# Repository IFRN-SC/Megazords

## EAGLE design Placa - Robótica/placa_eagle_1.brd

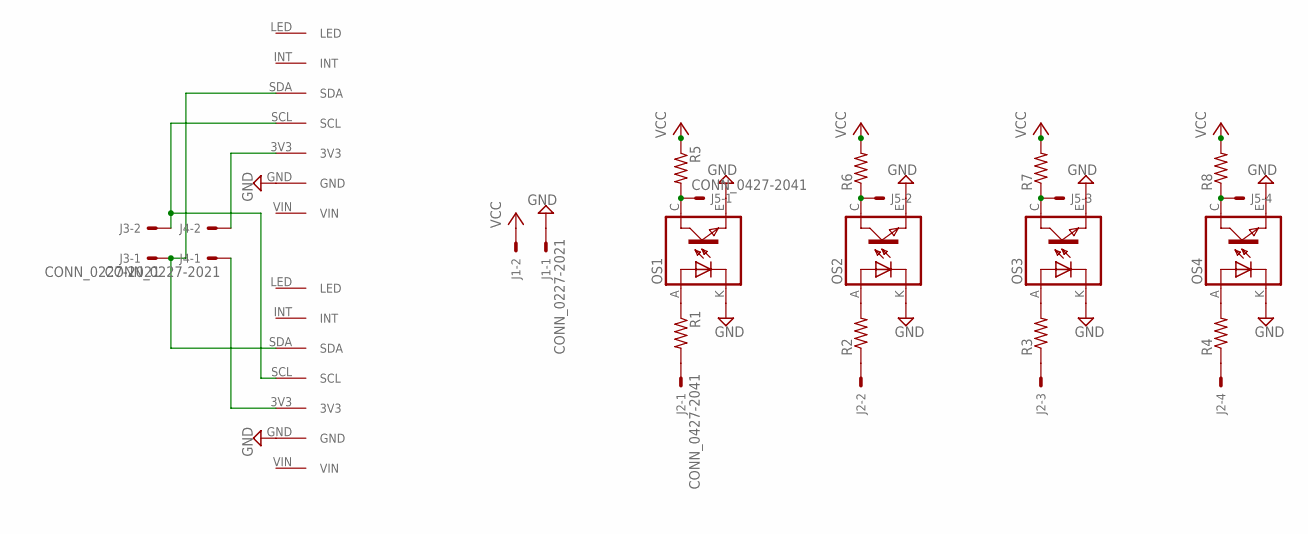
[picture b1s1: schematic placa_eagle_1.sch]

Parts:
J1, J3, J4: CONN_0227-2021; 6410-02
J2, J5: CONN_0427-2041; 6410-04
OS1, OS2, OS3, OS4: TCRT5000
R1, R2, R3, R4, R5, R6, R7, R8: R-US_0204/7; 0204/7
TCS1, TCS2: TCS34725

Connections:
GND: J1.1, OS1.E (EMITTER), OS1.K (CATHODE), OS2.E (EMITTER), OS2.K (CATHODE), OS3.E (EMITTER), OS3.K (CATHODE), OS4.E (EMITTER), OS4.K (CATHODE), TCS1.GND, TCS2.GND
unnamed: OS1.A (ANODE), R1.1
unnamed: OS2.A (ANODE), R2.2
unnamed: OS3.A (ANODE), R3.2
unnamed: OS4.A (ANODE), R4.2
unnamed: J5.1, OS1.C (COLLECTOR), R5.2
unnamed: J5.2, OS2.C (COLLECTOR), R6.1
unnamed: J5.3, OS3.C (COLLECTOR), R7.1
unnamed: J5.4, OS4.C (COLLECTOR), R8.1
unnamed: J2.1, R1.2
unnamed: J2.2, R2.1
unnamed: J2.3, R3.1
unnamed: J2.4, R4.1
unnamed: J4.2, TCS1.3V3
unnamed: J4.1, TCS2.3V3
unnamed: J3.1, TCS1.SDA, TCS2.SDA
unnamed: J3.2, TCS1.SCL, TCS2.SCL
VCC: J1.2, R5.1, R6.2, R7.2, R8.2

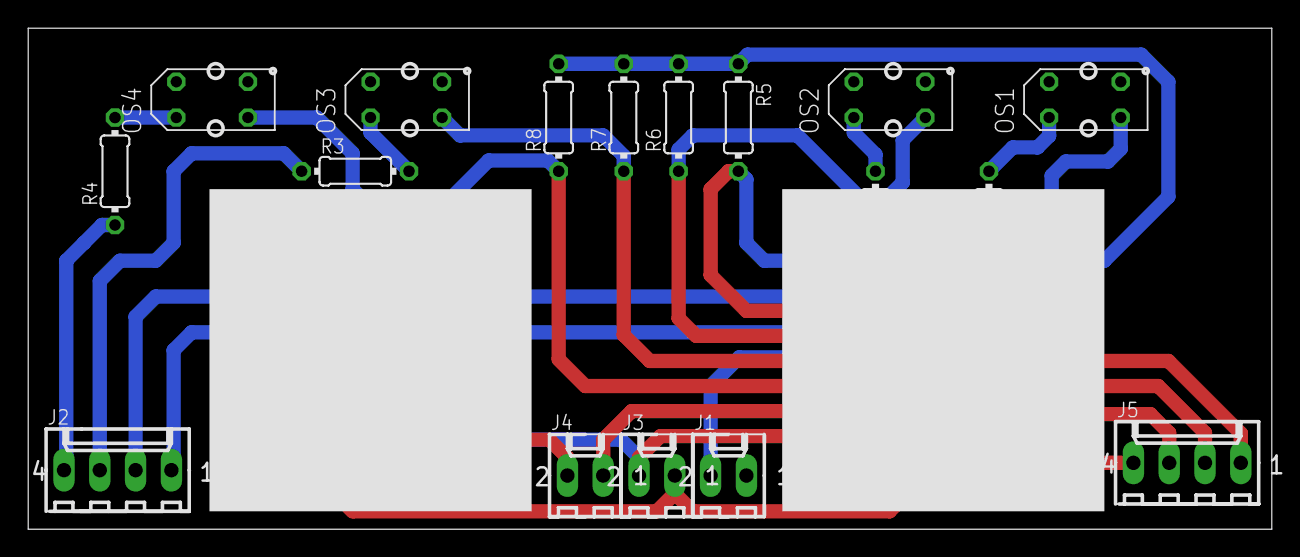
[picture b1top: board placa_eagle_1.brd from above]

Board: 2 copper layers, 88.2 x 35.5 mm, 19 parts (0 on the bottom side), 18 nets.

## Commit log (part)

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2018-04-11 Adcionando um novo codigo
2018-04-11 Uma pasta foi modificada
2018-04-11 Os valores de tensao dos motores foram modificados
2018-04-11 Foram adicionados as primeiras classes orientadas a objetos
2018-04-12 Alteração no comentario
2018-04-12 deixe de onda
2018-04-12 modifição na ordem das funcoes dos sensores
2018-04-16 Começo de codigo na função seguirLinha da classe estrategia
2018-04-16 Descomentei o codigo das funcoes dos sensores mais esquerdo e mais direito
2018-04-16 adcionei o objeto da classe Sensores nas funcoes de seguir linha
2018-04-17 Criação da classe Movimento
2018-04-17 Foi adcionada a função branco_branco_preto_preto_branco
2018-04-17 Foi criado um objeto da classe Movimento
2018-04-17 mudança das funcoes privadas para publicas e acrescimo da funcao parar
2018-04-17 Alteracao nos valores das medias
2018-04-18 transformei as funções para definir o branco de private para public
2018-04-18 Foi adcionado a função BPPB e as constantes repetidas de outra classe foram excluídas
2018-04-18 Foi criada a função voltar
2018-04-25 Calibracao foi incluido na classe Sensores, e um objeto foi criado
2018-05-04 Adição do codigo do sonar
2018-05-08 Foi adcionada a funcao detectouObstaculo
2018-05-09 Foi criada a classe Sensores.cpp
2018-05-09 moveu codigo sensores->estrategia
    foi realizada a mudança do código da classe sensores para a classe estratégia. Com isso foi necessário mudar funções de privada para pública
2018-05-10 Alteração no valor das medias dos sensores de refletancia e na posiçao da chave da função detectouObstaculo
2018-05-10 Foi adicionada a funcao desviarOPbstaculo dentro da funcao executar
2018-05-10 alteração nos valores das medias dos sensores de refletancia
2018-05-15 mudei o valor da constante PNEU_VOLTA
2018-05-15 sensores de refletância
    foi adicionado cinco funções para seguir linha.
2018-05-15 desviar obstaculo
    foi adicionado as funções da classe movimento no código de desviar obstaculo, e foi ajustado os valores para a execução do desviar.
2018-05-15 Criação do arquivo de Calibracao
2018-05-15 os dados foram movidos para o arquivo Calibracao.cpp
2018-05-15 desviar obstaculo
    foi regulado os valores para a execução de desviar o obstaculo.
2018-05-15 mudei o valor da constante PNEU_ANDA e PNEU_VOLTA
2018-05-15 foi ajustado o valor do delay
2018-05-23 desviar obstaculo
    foi iniciado o codigo de desviar obstaculo utilizando o sonar lateral
2018-05-23 moviento
    mudei os valores do robo.acionarMotores
2018-06-05 inclusao da classe Calibracao e uso da funcao
2018-06-05 Criação de funcoes
2018-06-05 Uso da função MediaEsquerdo
2018-06-11 verde
    foi dado inicio na criação do código para a indentificação do verde.
2018-06-11 foi ajustado a calibração do robô
2018-06-11 foi adicionado o robo.habilitaTCS34();
2018-06-11 Alteracao na visibilidade e definicao de #ifndef
2018-06-11 uso da funcao calibrar
2018-06-11 Heranca de Calibracao
2018-06-11 foi chamada o metodo calibracao de Estrategia
2018-06-12 mudados os valores da calibração
2018-06-13 Mudanca de local no codigo
2018-06-13 Criaacao de uma funcao construtor, uso desse construtor, salvando dados na eeprom
2018-06-14 Comando descomentado e exclusao de Print
2018-06-14 Criação da função dadosCalibracao e esclusão de codigo comentado
2018-06-14 implementação de dados na função dadosCalibracao
2018-06-15 Mudança no tipo de returno das funcoes
2018-06-15 Mudança nos valores de tenssão dos motores, alteracao na funcao calibracao
2018-06-15 Alteração nos valores da media
2018-06-15 Aprimoramento de algumas funções
2018-06-15 refletância
    foi aprimorado uma parte do código para que o robô faça o verde com os sensores de refletância.
2018-06-15 Alteração no nome da função
2018-06-18 foi alterado o valor da função girarSoEsqueda
2018-06-18 desviar obstáculo
    foi ajustado o código para o melhor desempenho no desviar obstáculo
2018-06-26 Fechamento da chave
2018-07-31 alteração nos delay
2018-07-31 configurei o Serial
2018-07-31 definiçao de funcao calibreBrancos();
2018-07-31 Inicio do novo codigo de Calibracao
2018-08-21 Alteração dos Leds
2018-08-21 Alteração no while fim de pista
2018-09-12 verde:
    foi feito um pequeno código para a indentificação do verde.
2018-09-14 foi corrigido alguns erros no código
2018-09-14 obstáculo
    foi ajustado alguns valores no código de desviar obstáculo
2018-09-17 verde
    foi criado um código para testar o verde.
2018-09-18 verde
    foi ajustado as condições para função testaVerde.
2018-10-09 foi ajustado alguns valores dos delays
2018-10-09 foi feito as condições para o verde
2018-10-09 foi feito os codigos para girar no verde
2018-10-09 foi feito um codigo para ler os valores dos sensores de cor
2018-10-16 foi adicionado mais condições para testar verde
2018-10-16 foi feito 3 funções para girar no verde
2018-10-16 foi ajustado algumas partes do codigo
2018-10-16 foi apagado uma parte do codigo que estava errado
2018-10-18 Alteração no nome das variaveis
2018-10-18 Criacao de duas novas variaveis
2018-10-19 foi apagado um comtentario
2018-10-25 foi fito pequenos ajustes no codigo
2018-10-29 foi retirado algumas funções que não eram usadas e também foi feitos pequenos ajustes no desviar obstaculo.
2018-10-29 foi feito alguns ajustes no código
2018-10-29 foi retirado algumas funções que não eram usadas.
2018-10-29 verde
    foi ajustado a condição para testar o verde.
2018-10-31 foi ajustado o delay do desviar obstáculo.
2018-10-31 foi ajustado o código para fazer as curvas.
2019-03-11 Placa:
    foi alterado a distância dos sensores
2019-03-11 Revert "Placa:"
    This reverts commit bff0d93cbbb8e7f4ec67e0c019f49b1a51a922fc.
2019-03-18 movimento:
    foi ajustado a velocidade para os novos motores.
2019-03-18 .ino:
    foi retirado um comentario.
2019-03-18 movimento:
    foi feito uma costante para cada motor, e implementadas nas funções de mivimentos.
2019-03-18 estrategia:
    foi ajustado dos delays do obstaculo.
2019-04-02 códigos para a sala 3
2019-04-05 habilitamos o sensor de cor TCS34
2019-04-05 criação de constantes para os ângulos de cada servo
2019-04-05 fizemos com que o robô volte a posição de inicio após deixar a bolinha
2019-04-05 modifiquei o nome de alguns métodos e fiz comentários
2019-04-05 modifiquei o alinhamento do robô
2019-04-05 exclui o método de testa motores
2019-04-05 mudei o encapsulmento dos métodos
2019-04-13 mudamos a estrategia para identificar a area de resgate
2019-04-13 mudamos a estrategia para identificar a zona
2019-04-14 comentei onde identificamos a entrada da sala três
2019-04-14 correção de erros não visto antes
2019-04-14 modifiquei os ângulos dos servos para iniciar o robô
2019-04-17 alteração no ângulo da garra
2019-04-17 valores das constantes alterados
2019-04-29 foi alterado o angulo da garra
2019-04-30 foi criada a função para testar o verde
2019-04-30 foi criada as funções para girar nos respectivos verdes
2019-05-01 variáveis locais realocadas para o .h e strings para a memória flash
2019-05-08 foi corrigido as condições para indentificar o verde e foi adicionado o código caso não tenha verde.
2019-05-13 foi alterado na calibracao a leitura do s para o h do sensor de cor e ajustado o codico para o mesmo.
2019-05-15 foi retirado alguns erros no codigo.
2019-05-24 foi ajustado o codigo do desviar obstaculo.
2019-05-27 foi adicionado o codigo para fechar a garra enquanto o robo segue na sala.
2019-06-26 correção
    foi corrigido um erro.
2019-06-27 correção
    foi feito alguns ajustes no desviar obstáculo.
2019-06-27 obstáculo
    foi alterado o código do desviar obstáculo.
2019-06-27 garra
    foi alterado alguns valores das funções.
2019-07-03 RAMPA
    foi ajustado o valor para indentificar a rampa.
2019-07-03 RESGATE
    foi ajustado alguns delays para que o robô percorra a sala 3 mais rápido.
2019-07-04 OBSTÁCULO
    foi ajustado o desviar obstáculo.
2019-07-04 RESGATE SALA 3
    foi ajustado alguns delays.
2019-07-04 VERDE
    foi criado duas funções para o verde.
2019-07-04 CALIBRAÇÃO
    foi feita algumas alterações para ler o valor do .s do sensor de cor.
2019-07-05 CALIBRAÇÃO
    foi feito alguns ajustes para que a calibração seja salva corretamente.
2019-07-05 CALIBRAÇÃO
    foi cridado uma nova função para salvar a calibração.
2019-07-05 AJUSTES
    foi ajustado os delays do servo da garra.
2019-07-05 AJUSTES
    foi ajustado os valores das constantes de movimento.
2019-07-19 mudei
2019-07-19 CALIBRAÇÃO
    - print nos valores da calibração
2019-07-19 VERDE
    foi feito o código do verde.
2019-07-19 SENSORES
    foi excluido algumas funções que não eram utilizadas.
2019-07-23 ESTRATÉGIA
    foi ajustado os delays dos motores.
2019-07-23 RESGATE
    foi ajustado o código para a movimentação do robô na terceira sala.
2019-07-23 RESGATE.H
    foi adicionado uma nova função.
2019-07-23 .INO
    ajuste de um parametro
2019-07-24 RESGATE
    ajustes para melhor mobilidade na terceira sala.
2019-07-31 Diminui o espaço de armazenamento para programas utilizando o (F("")).
2019-08-21 DESVIAR OBSTÁCULO
    foi ajustado o código para que o robô desvie com uma maior facilidade.
2019-08-22 RESGATE.H
    foi criado duas funções para quando a rampa estiver no lado direito da terceira sala.
2019-08-22 RESGATE.CPP
    foi criado uma condição para a indentificação de qual lado o robô está entrando na terceira sala e foi criado o espelo do código de entrar na sala.
2019-08-26 OBSTACULO
    foi ajustado o codigo para o pior caso do desviar obstaculo.
2019-08-29 TERCEIRA SALA
    foi ajustado o código para a área na posição "a" para quando a entrada na sala for pela direita.
2019-08-29 SALA3
    foi feito alguns ajustes
2019-08-30 INO. modifiquei o ângulo da garra
2019-08-30 Adicionei uma nova função após ela parar de seguir na sala, o mesmo ira voltar ao ponto zero
2019-08-30 modifiquei o método para fazer o verde
2019-08-30 AJUSTE
2019-08-31 VERDE
    ajustes no verde
2019-09-02 Garra.h adicionei os valores antigos as constantes
2019-09-02 Resgate.cpp tive a ideai de ajustar a sala 3 para quaisquer tipos de sala ou zona, tendo em mente como o robô ira identificar ambas
2019-09-02 Stuart.ino formatei o codigo
2019-09-02 processo de construção da sala de resgate
2019-09-02 progreso na sala 3
2019-09-03 GARRA.H criei um método que fecha a garra em movimento
2019-09-03 adicionamos o método para fechar a garra em movimento na area de resgate
2019-09-03 deixei um código comentado sobre fechar a garra enquanto o robô se movimentava
2019-09-23 .INO
    ajuste no ângulo da garra.
2019-09-23 RESGATE
    implementação de uma nova função para fechar a garra enquanto o robô se movimenta.
2019-09-23 Update Stuart.ino
    Ajustei o ângulo da garra após o robô ser ligado
2019-09-23 Update Garra.h
    modificação no angulo da nova garra
2019-09-23 Update Sensores.h
    modifiquei a identação do código
2019-09-23 Update Estrategia.cpp
    habilitei o uso do sensor de cor
2019-09-23 Update Estrategia.cpp
    modifiquei a identação do código
2019-09-23 Update Estrategia.h
    mudei a identação do código
2019-09-24 Criei uma constante para armazenar o valor da distancia do robô com a area de regate
2019-09-24 ajustes na sala 3
2019-09-26 GARRA.CPP - adicionei um novo método para soltar a bolinha
2019-09-26 GARRA.H - modifiquei o valor da constante delay
2019-09-26 RESGATE.CPP - ajustei alguns métodos para facilitar a compreensão do código
2019-09-29 Alterei ângulo da garra
2019-09-29 Apaguei comentarios desnecessários e criei alguns métodos
2019-10-01 hb20
2019-10-14 Adicionei uma função para a posição da garra quando o robô iniciar
2019-10-14 RESGATE
    ajuste no código de voltar para o ponto zero.
2019-10-15 RESGATE
    ajuste no código da sala 3
2019-10-15 RESGATE.H implementei o método aposVarrerSala para o procurar a vitima onde não foi preenchido
